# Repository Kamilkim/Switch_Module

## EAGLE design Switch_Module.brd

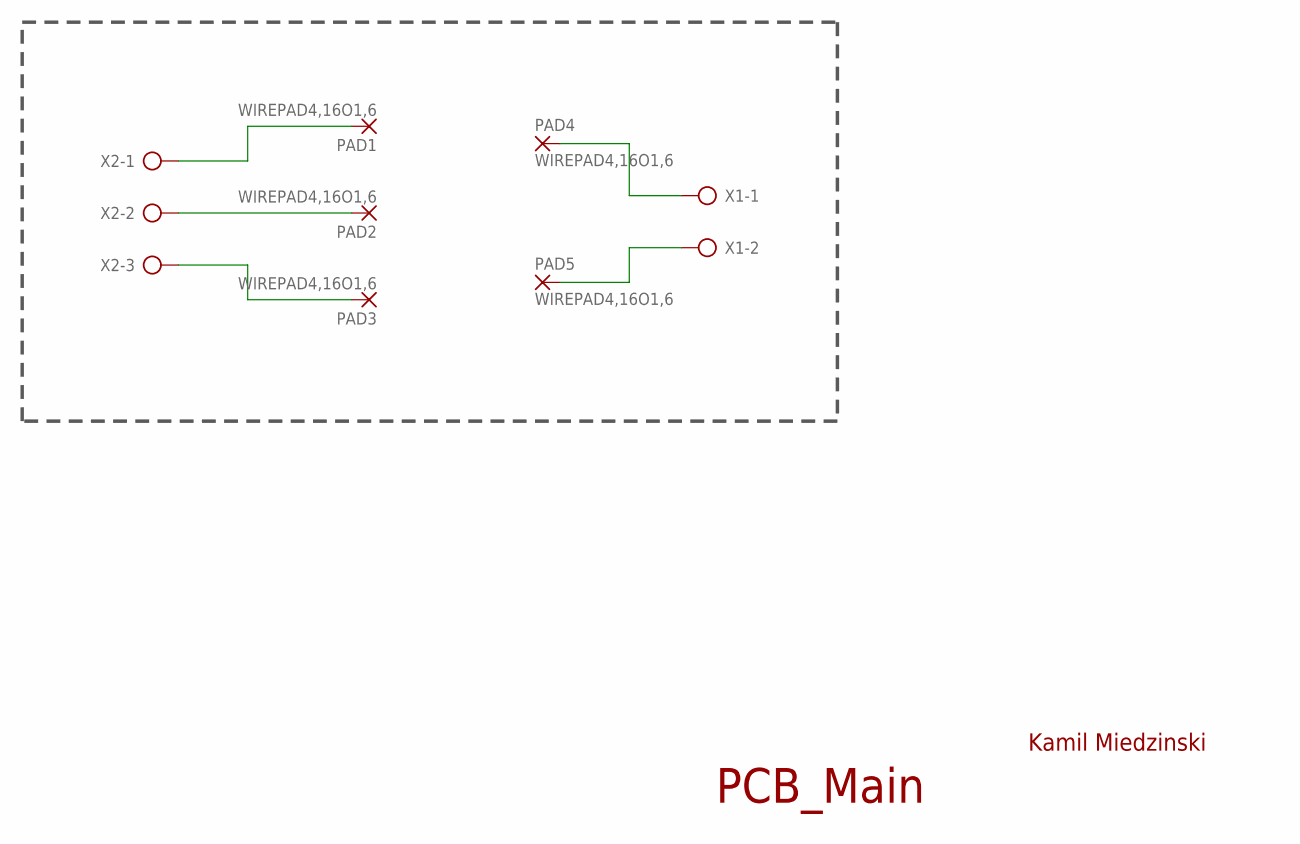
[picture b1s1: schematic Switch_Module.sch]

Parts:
PAD1, PAD2, PAD3, PAD4, PAD5: WIREPAD4,16O1,6; 4,16O1,6
X1: GMKDSP_3/2
X2: MKDS_3/3

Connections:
unnamed: PAD1.1, X2.1
unnamed: PAD2.1, X2.2
unnamed: PAD3.1, X2.3
unnamed: PAD4.1, X1.1
unnamed: PAD5.1, X1.2

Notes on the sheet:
Kamil Miedzinski
PCB_Main

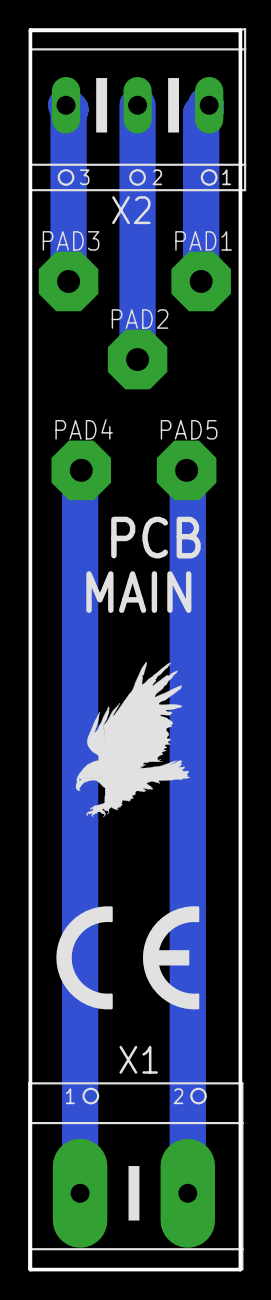
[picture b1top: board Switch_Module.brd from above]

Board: 2 copper layers, 14.7 x 86.6 mm, 9 parts (0 on the bottom side), 5 nets.

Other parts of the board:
U$1: CE_7.3MM
U$2: EAGLE-PLC-8MM

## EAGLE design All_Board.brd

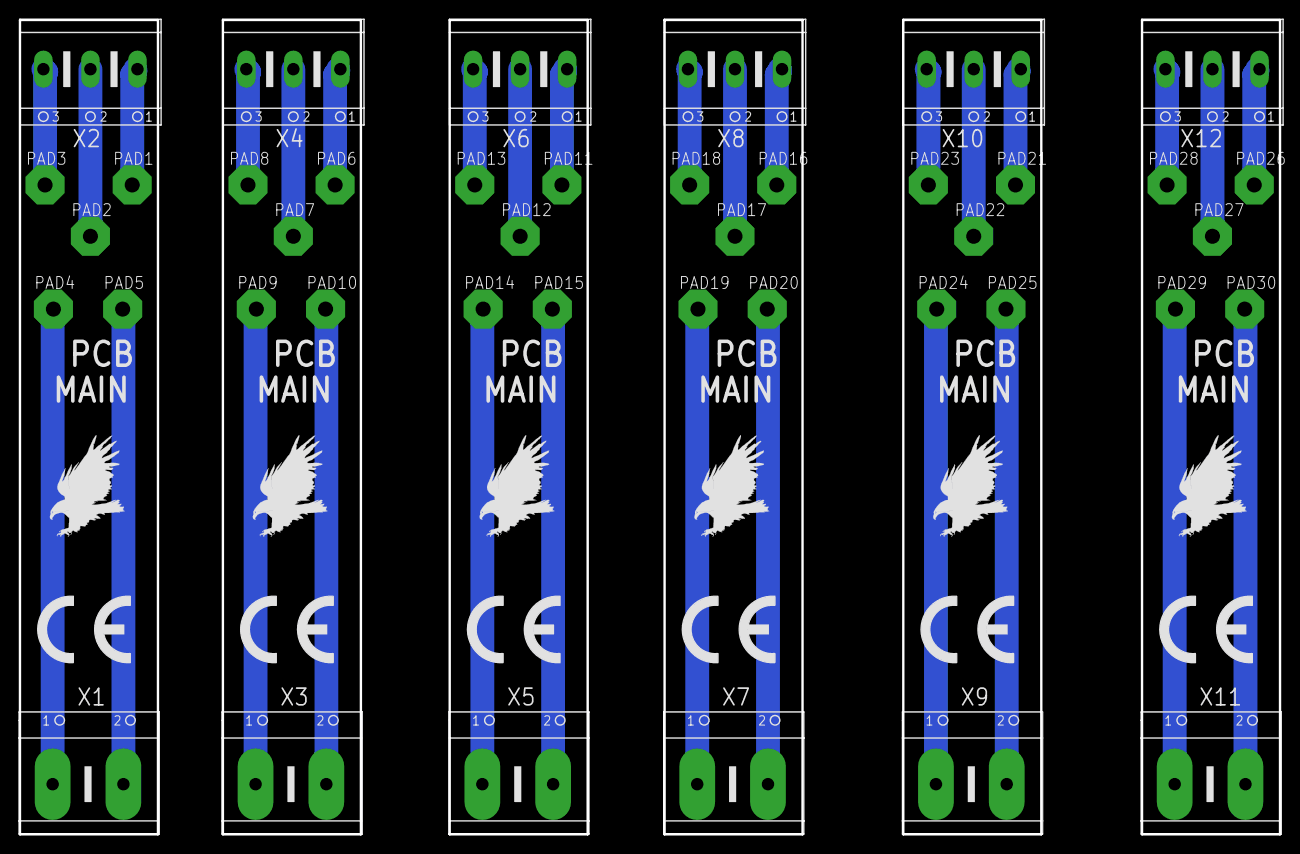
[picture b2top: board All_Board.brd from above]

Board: 2 copper layers, 134.1 x 86.6 mm, 54 parts (0 on the bottom side), 30 nets.

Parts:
PAD1, PAD2, PAD3, PAD4, PAD5, PAD6, PAD7, PAD8, PAD9, PAD10, PAD11, PAD12, PAD13, PAD14, PAD15, PAD16, PAD17, PAD18, PAD19, PAD20, PAD21, PAD22, PAD23, PAD24, PAD25, PAD26, PAD27, PAD28, PAD29, PAD30: WIREPAD4,16O1,6; 4,16O1,6
U$1, U$3, U$5, U$7, U$9, U$11: CE_7.3MM
U$2, U$4, U$6, U$8, U$10, U$12: EAGLE-PLC-8MM
X1, X3, X5, X7, X9, X11: GMKDSP_3/2
X2, X4, X6, X8, X10, X12: MKDS_3/3

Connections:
unnamed: PAD1.1, X2.1
unnamed: PAD2.1, X2.2
unnamed: PAD3.1, X2.3
unnamed: PAD4.1, X1.1
unnamed: PAD5.1, X1.2
unnamed: PAD9.1, X3.1
unnamed: PAD10.1, X3.2
unnamed: PAD6.1, X4.1
unnamed: PAD8.1, X4.3
unnamed: PAD7.1, X4.2
unnamed: PAD14.1, X5.1
unnamed: PAD15.1, X5.2
unnamed: PAD11.1, X6.1
unnamed: PAD13.1, X6.3
unnamed: PAD12.1, X6.2
unnamed: PAD19.1, X7.1
unnamed: PAD20.1, X7.2
unnamed: PAD16.1, X8.1
unnamed: PAD18.1, X8.3
unnamed: PAD17.1, X8.2
unnamed: PAD24.1, X9.1
unnamed: PAD25.1, X9.2
unnamed: PAD21.1, X10.1
unnamed: PAD23.1, X10.3
unnamed: PAD22.1, X10.2
unnamed: PAD29.1, X11.1
unnamed: PAD30.1, X11.2
unnamed: PAD26.1, X12.1
unnamed: PAD28.1, X12.3
unnamed: PAD27.1, X12.2

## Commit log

2019-11-09 Image
2019-11-09 Image added
2019-11-22 poprawnik przed drukowaniem
